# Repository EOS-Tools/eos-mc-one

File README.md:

# Introduction

The repository contains the eagle files for an ardunio uno clone with small size. The design imphasizes on production ready design. Users can design hats for the device.

## Models

### EOS MC ONE SMD (Without Programmer)

#### Top View

#### Bottom View

#### Drill View

### EOS MC ONE (Without Programmer)

#### Top View

#### Bottom View

#### Drill View

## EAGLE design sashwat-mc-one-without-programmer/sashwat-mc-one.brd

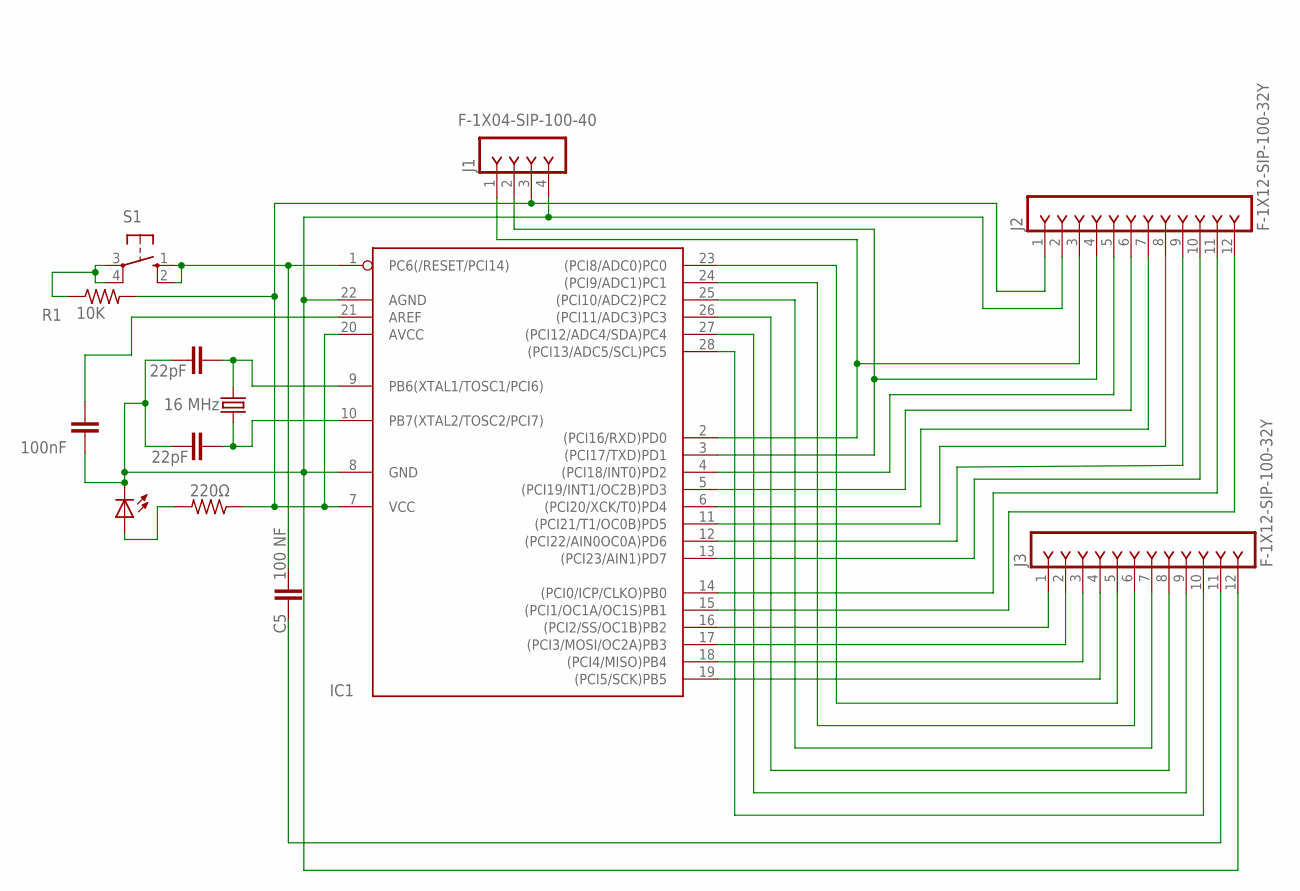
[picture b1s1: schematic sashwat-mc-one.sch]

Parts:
C1, C2: 22pF; C2.5-3
C3: 100nF; C2.5-3
C5: 100 NF; C2.5-3
IC1: ATMEGA328-20P; DIL28-3
J1: F-1X04-SIP-100-40; SIP-100-04-40
J2, J3: F-1X12-SIP-100-32Y; SIP-100-12-32Y
LED3: LED5MM
Q1: 16 MHz; HC49/S
R1: 10K; 0805-THM
R5: 220Ω; 0805-THM
S1: 10-XX; B3F-10XX

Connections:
unnamed: C1.2, IC1.9 (PB6(XTAL1/TOSC1/PCI6)), Q1.2
unnamed: C2.2, IC1.10 (PB7(XTAL2/TOSC2/PCI7)), Q1.1
unnamed: LED3.A, R5.2
unnamed: C1.1, C2.1, C3.1, IC1.8 (GND), IC1.22 (AGND), J1.4, J2.2, J3.12, LED3.K (C)
unnamed: IC1.4 ((PCI18/INT0)PD2), J2.5
unnamed: IC1.2 ((PCI16/RXD)PD0), J1.1, J2.3
unnamed: IC1.3 ((PCI17/TXD)PD1), J1.2, J2.4
unnamed: IC1.7 (VCC), IC1.20 (AVCC), J1.3, J2.1, R1.2, R5.1
unnamed: IC1.5 ((PCI19/INT1/OC2B)PD3), J2.6
unnamed: IC1.6 ((PCI20/XCK/T0)PD4), J2.7
unnamed: IC1.11 ((PCI21/T1/OC0B)PD5), J2.8
unnamed: IC1.12 ((PCI22/AIN0OC0A)PD6), J2.9
unnamed: IC1.13 ((PCI23/AIN1)PD7), J2.10
unnamed: IC1.14 ((PCI0/ICP/CLKO)PB0), J2.11
unnamed: IC1.15 ((PCI1/OC1A/OC1S)PB1), J2.12
unnamed: IC1.16 ((PCI2/SS/OC1B)PB2), J3.1
unnamed: IC1.17 ((PCI3/MOSI/OC2A)PB3), J3.2
unnamed: IC1.18 ((PCI4/MISO)PB4), J3.3
unnamed: IC1.19 ((PCI5/SCK)PB5), J3.4
unnamed: IC1.23 ((PCI8/ADC0)PC0), J3.5
unnamed: IC1.24 ((PCI9/ADC1)PC1), J3.6
unnamed: IC1.25 ((PCI10/ADC2)PC2), J3.7
unnamed: IC1.26 ((PCI11/ADC3)PC3), J3.8
unnamed: IC1.27 ((PCI12/ADC4/SDA)PC4), J3.9
unnamed: IC1.28 ((PCI13/ADC5/SCL)PC5), J3.10
unnamed: C5.1, J3.11
unnamed: C5.2, IC1.1 (PC6(/RESET/PCI14)), S1.1 (S), S1.2 (S1)
unnamed: C3.2, IC1.21 (AREF)
unnamed: R1.1, S1.3, S1.4 (P1)

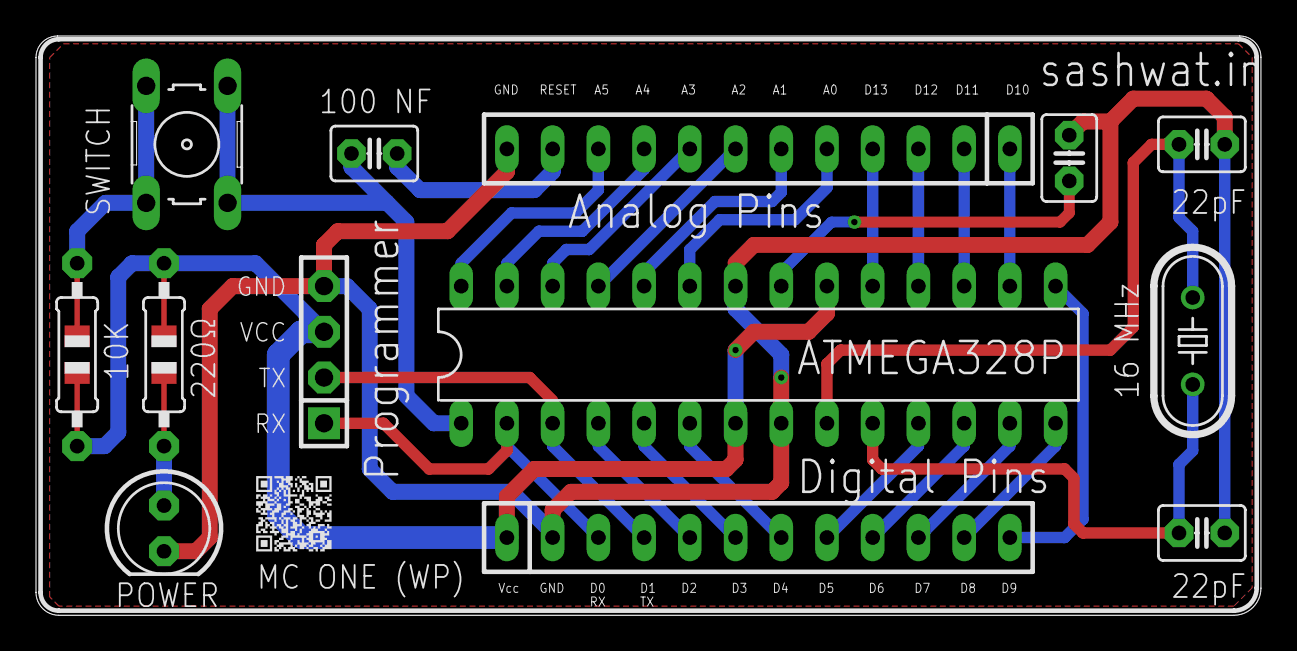
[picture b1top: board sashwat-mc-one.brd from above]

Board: 2 copper layers, 68.1 x 32.2 mm, 13 parts (0 on the bottom side), 29 nets.

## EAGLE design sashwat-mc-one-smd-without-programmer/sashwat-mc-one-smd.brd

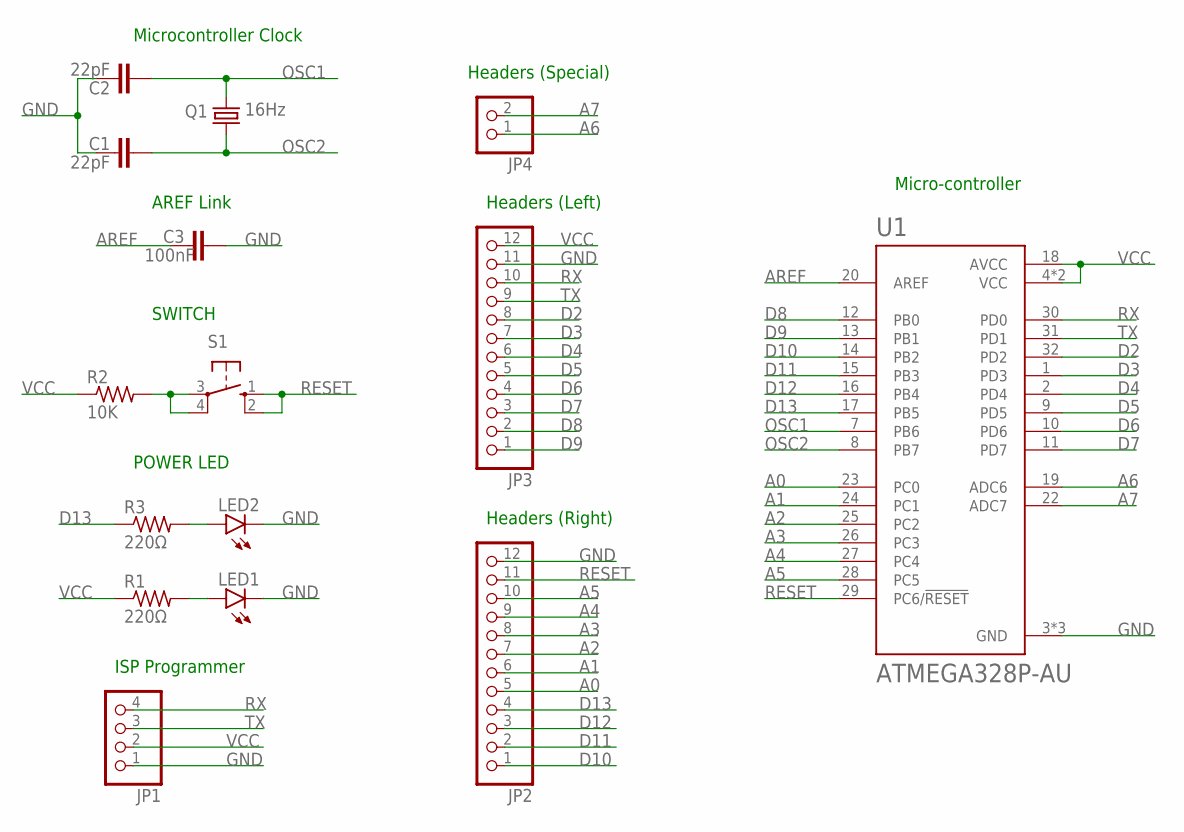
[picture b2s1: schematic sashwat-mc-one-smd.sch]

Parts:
C1, C2: 22pF; C0805
C3: 100nF; C0805
JP1: PINHD-1X4; 1X04
JP2, JP3: PINHD-1X12; 1X12
JP4: PINHD-1X2; 1X02
LED1, LED2: LEDCHIPLED_0805; CHIPLED_0805
Q1: 16Hz; HC49/S
R1, R3: 220Ω; R0805
R2: 10K; R0805
S1: 10-XX; B3F-10XX
U1: ATMEGA328P-AU; QFP80P900X900X120-32N

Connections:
A0: JP2.5, U1.23 (PC0)
A1: JP2.6, U1.24 (PC1)
A2: JP2.7, U1.25 (PC2)
A3: JP2.8, U1.26 (PC3)
A4: JP2.9, U1.27 (PC4)
A5: JP2.10, U1.28 (PC5)
A6: JP4.1, U1.19 (ADC6)
A7: JP4.2, U1.22 (ADC7)
AREF: C3.2, U1.20 (AREF)
D2: JP3.8, U1.32 (PD2)
D3: JP3.7, U1.1 (PD3)
D4: JP3.6, U1.2 (PD4)
D5: JP3.5, U1.9 (PD5)
D6: JP3.4, U1.10 (PD6)
D7: JP3.3, U1.11 (PD7)
D8: JP3.2, U1.12 (PB0)
D9: JP3.1, U1.13 (PB1)
D10: JP2.1, U1.14 (PB2)
D11: JP2.2, U1.15 (PB3)
D12: JP2.3, U1.16 (PB4)
D13: JP2.4, R3.1, U1.17 (PB5)
GND: C1.2, C2.2, C3.1, JP1.1, JP2.12, JP3.11, LED1.C, LED2.C, U1.3 (GND), U1.5 (GND), U1.21 (GND)
unnamed: LED2.A, R3.2
unnamed: LED1.A, R1.2
unnamed: R2.2, S1.3, S1.4 (P1)
OSC1: C2.1, Q1.2, U1.7 (PB6)
OSC2: C1.1, Q1.1, U1.8 (PB7)
RESET: JP2.11, S1.1 (S), S1.2 (S1), U1.29 (PC6/!RESET)
RX: JP1.4, JP3.10, U1.30 (PD0)
TX: JP1.3, JP3.9, U1.31 (PD1)
VCC: JP1.2, JP3.12, R1.1, R2.1, U1.4 (VCC), U1.6 (VCC), U1.18 (AVCC)

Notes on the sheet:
ISP Programmer
POWER LED
SWITCH
Microcontroller Clock
AREF Link
Headers (Left)
Headers (Right)
Headers (Special)
Micro-controller

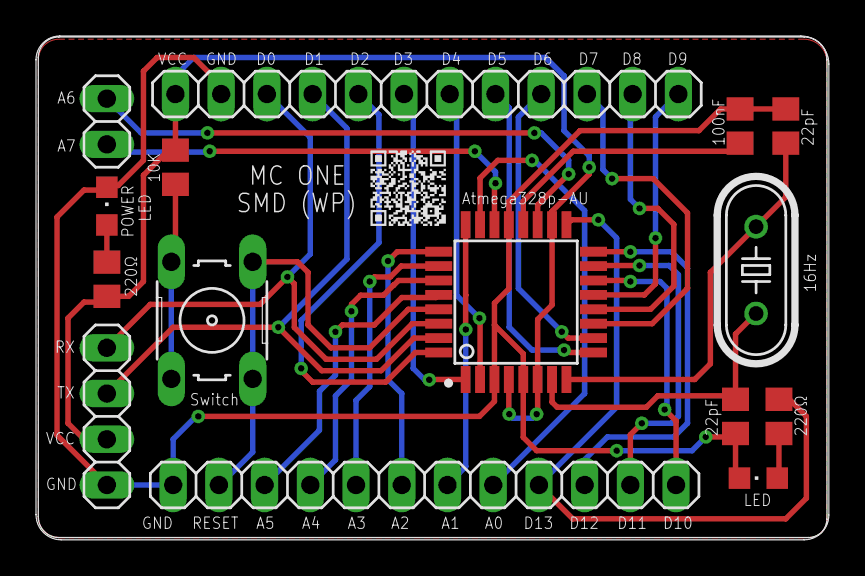
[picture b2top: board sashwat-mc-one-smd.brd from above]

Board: 2 copper layers, 44.0 x 28.0 mm, 15 parts (0 on the bottom side), 31 nets.

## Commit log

2021-05-02 added design and doc
2021-05-02 Updated design
2021-05-02 Made changes
2021-05-09 Added new design
2021-05-09 Increased track width
2021-05-09 Updated documentation
2021-05-09 Added .gitignore
2021-06-13 Added new code
2021-07-10 AUpdated docs
2021-08-04 Added smd schematics
2021-08-04 Removed unnecessary files
2021-08-07 Added SMD design
2021-08-07 Completed SMD design
2021-08-07 Updated doc
2021-08-07 Updated non smd design
2021-08-17 deleted unwanted
2022-05-03 Added PCB photos

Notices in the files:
parts and their libraries:
con-headers-jp: Copyright (C) 2008, Bob Starr
